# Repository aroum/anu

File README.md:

# Anu

[Anu](https://en.wikipedia.org/wiki/Anu) - compact stick mouse.

Gerber files and stl models can be downloaded in [releases](https://github.com/aroum/anu/releases).

# Features
* PSP analog stick 
* 3 keys, Kailh Choc V1 switches
* Choc spacing
* Direct pins 
* Wireless(optional)
* Per switch RGB(optional)
* Power switch for wireless controllers(optional)
* 100x100 mm panel pcb

# Firmware

Anu can be used with [nRFMicro](https://github.com/joric/nrfmicro) or [nice!nano](https://nicekeyboards.com/nice-nano/) and 301230 batteries for wireless mode. Currently ZMK does not support analog sticks.

The original idea was to create a compact "mouse" ([layout](http://www.keyboard-layout-editor.com/#/gists/458957846f6c65296a02e8bd9ae2c3ca)), but it can also be used as a gamepad. Gamepad firmare use [ArduinoGamepad library](https://github.com/gamelaster/ArduinoGamepad). For more detailed settings of the gamepad, you can use [TocaEdit XBOX 360 CE](https://www.x360ce.com/).

You can use the [threeboard layout](https://github.com/taylorconor/threeboard) to enter text using Anu.

Other configs using the analog stick [1](https://blog.ffff.lt/posts/joystick-algorithms/) & [2](https://github.com/CarrasTec/JoystickQMK/tree/main/macrokrs).

Work on ZMK support is also [in progress](https://github.com/aroum/zmk-anu/).

# BOM

| Item                                                                   | Quantity | Remarks                            |
| ---------------------------------------------------------------------- | -------: | ---------------------------------- |
| [proMicro](https://aliexpress.ru/item/32840365436.html)                |        1 | or any other compatible controller |
| [Kailh Choc V1](https://aliexpress.ru/item/32959996455.html)           |        3  switches                            |
| [FJ08K-S](https://aliexpress.ru/item/1005006435837883.html) or [FJ08K](https://aliexpress.ru/item/32979957864.html)    |       1 | analog stick. FJ08K-S has an additional button  |
| [Keycaps](https://aliexpress.ru/item/33026798318.html)                 |       3 | 1U                                 |
| [YS-SK6812MINI-E](https://aliexpress.ru/item/4000475685852.html)       |       3 | RGB leds                           |
| [Magnets](https://aliexpress.ru/item/1005002757445161.html)            |      3-5 | disc 7x2 mm (for case)             |
| [Bumpon](https://aliexpress.ru/item/4001188580018.html)                |        8 | 5x2 mm                             |
| [Sockets PH3.5](https://aliexpress.ru/item/32899635835.html)           |     12x2 | for controller                     |
| [SMD button 3x4x2mm](https://aliexpress.ru/item/1005003812819985.html) |        1 | for reset                          |
| [MSK-12C02](https://aliexpress.ru/item/1005001398386692.html)          |        1 | Power switch  (wireless only)      |
| [301230](https://aliexpress.ru/item/32732458079.html)                  |        1 | Battery  (wireless only)           |
| [m2 nuts](https://aliexpress.ru/item/1005003114659036.html)            |        4 | for case                           |
| [m2x4 screws](https://aliexpress.ru/item/1005004494509456.html)        |        4 | for case                           |

[IBOM](https://htmlpreview.github.io/?https://github.com/aroum/anu/blob/master/pcb/ibom/ibom.html)

# Build guide
1. Solder the controller sockets
2. Solder the power switch (wireless only)
3. Solder the reset button
4. Solder the battery (only for wireless version)
5. Solder analog stick
6. Solder the pins into the controller
7. Solder 3 Kailh Choc V1 switches 
8. Solder 3 LEDs (RGB version only)
9. Put the keycaps on the switches and analog stick
10. Stick bumpon or place the keyboard in the case
11. Insert controller into sockets
12. Flash the bootloader (see the official manual for the controller)
13. Flash the firmware (see the official manual for the controller)

[Soldering Tutorial for Beginners](https://mightyohm.com/files/soldercomic/FullSolderComic_EN.pdf) ([RU version](https://sho0.neocities.org/downloads/komiks_payat_prosto.pdf))

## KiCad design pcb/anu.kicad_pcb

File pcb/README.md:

# PCB

There is also the option of two PCBs fitted into 100x100 mm.

Gerber files can be downloaded in [releases](https://github.com/aroum/anu/releases).

[IBOM](https://htmlpreview.github.io/?https://github.com/aroum/anu/blob/master/pcb/ibom/ibom.html)

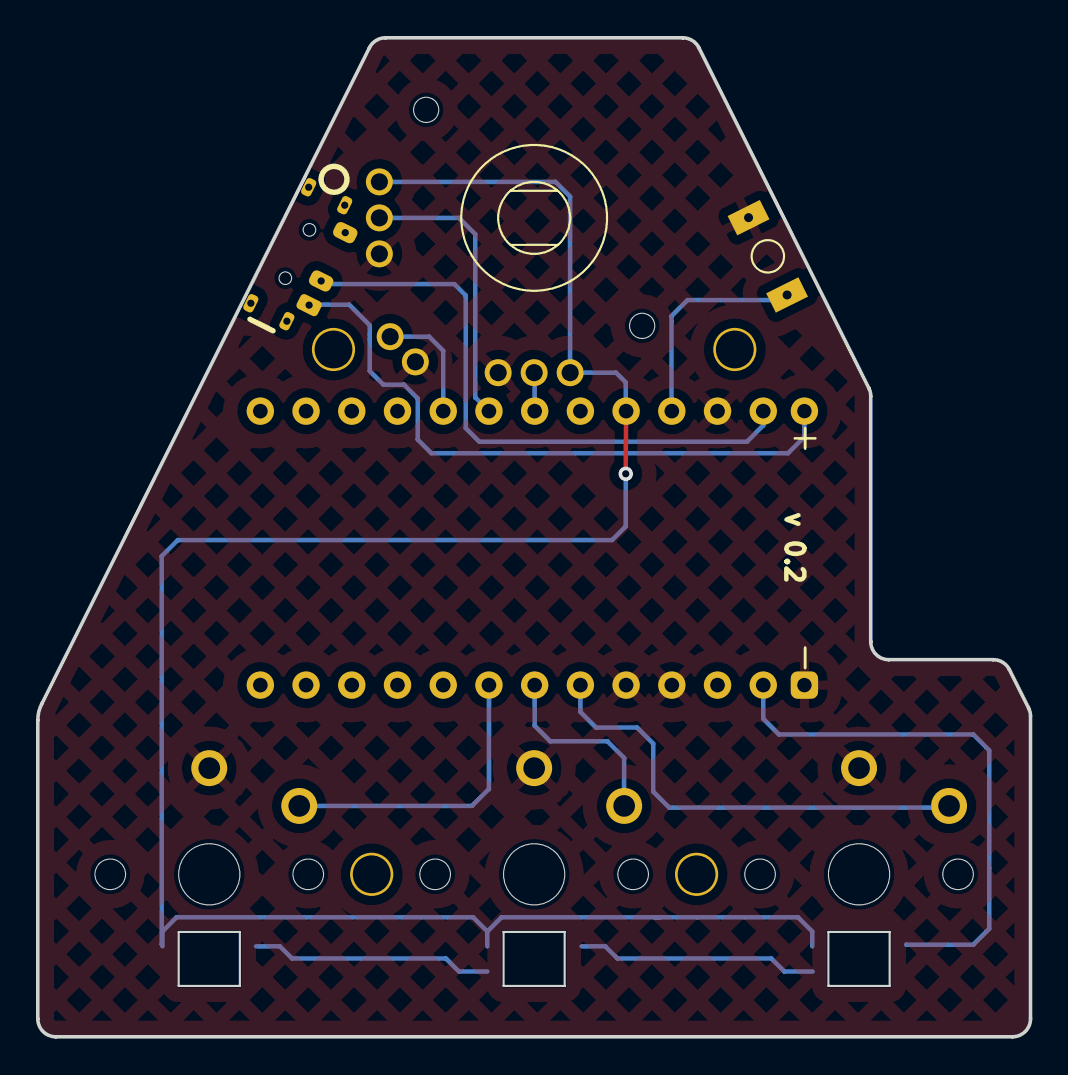
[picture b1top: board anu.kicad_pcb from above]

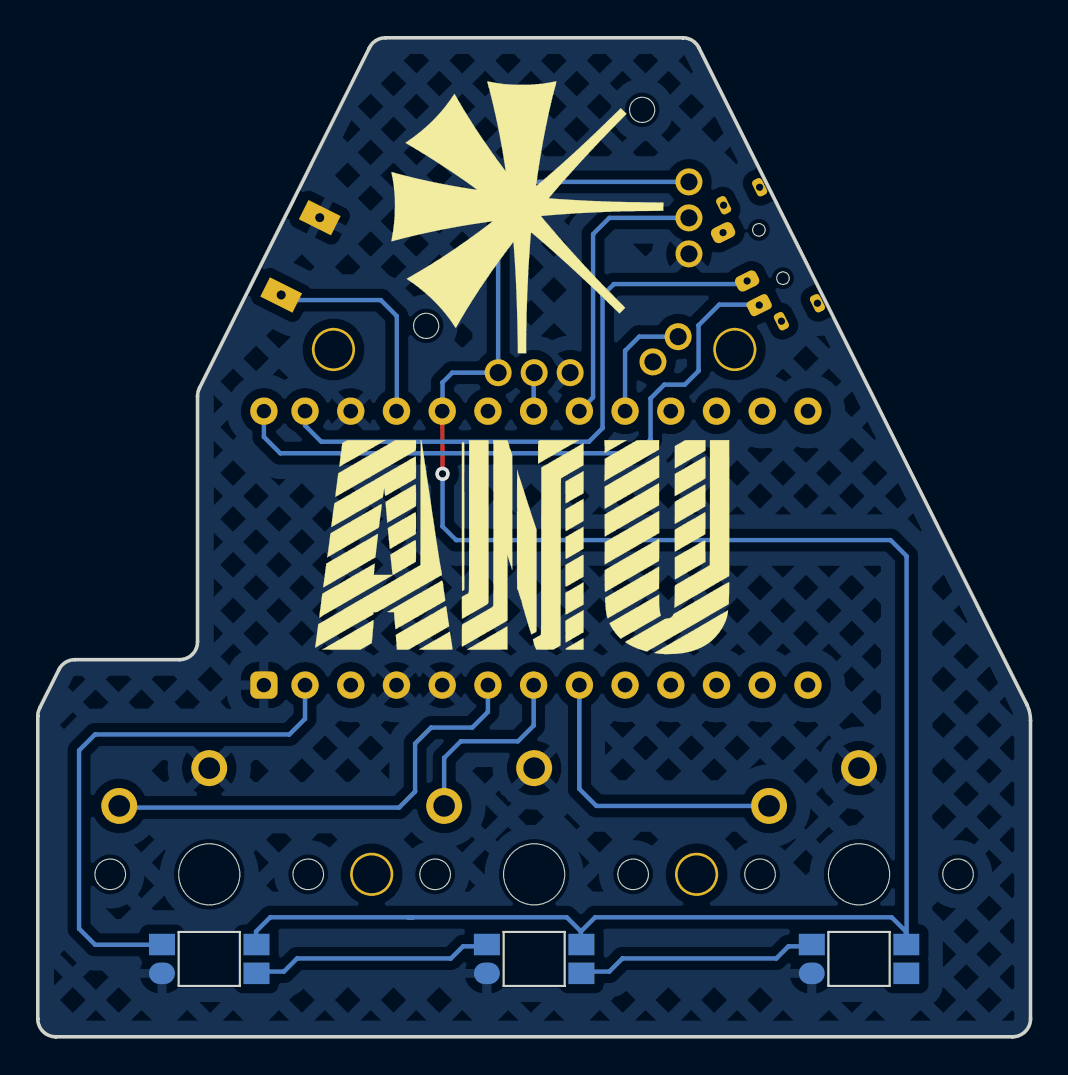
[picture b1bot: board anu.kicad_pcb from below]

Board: 2 copper layers, 55.2 x 55.5 mm, 17 parts (5 on the bottom side), 14 nets.

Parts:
G1: Logo; Logo_anu_cuneiform
G2: Logo; Logo_anu
H1, H1#2, H1#3, H1#4: Hole; HOLE
J1: battery connector; battery_conn_duplex
LED1, LED2, LED3: YS-SK6812MINI-E; YS-SK6812MINI-E_small
RSW1: SW_PUSH; SW_3x4x2_2legs
SW1, SW2, SW3: SW_PUSH; ChocV1_1u
SW4: SW_SPDT; SW_MSK-12C02_duplex
U1: ProMicro_r; ProMicro_v4
X1: FJ08K-S

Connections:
GND: J1.2, LED1.3 (GND), LED2.3 (GND), LED3.3 (GND), RSW1.2, SW1.2, SW2.2, SW3.2, U1.3 (GND), U1.4 (GND), U1.23 (GND), X1.A (SW1), X1.X3 (VCC), X1.Y1 (VCC)
LED: LED3.4 (DIN), U1.1 (D3/TX0)
unnamed: J1.1, SW4.3 (C)
unnamed: LED1.4 (DIN), LED2.2 (DOUT)
unnamed: LED2.4 (DIN), LED3.2 (DOUT)
VBAT: SW4.2 (B), U1.24 (RAW)
VCC: LED1.1 (VDD), LED2.1 (VDD), LED3.1 (VDD), U1.21 (VCC), X1.X1 (GND), X1.Y3 (GND)
analogX: U1.18 (A1/F6), X1.X2 (outX)
analogY: U1.19 (A2/F5), X1.Y2 (outY)
reset: RSW1.1, U1.22 (RST)
sw1: SW1.1, U1.7 (D4/4)
sw2: SW2.1, U1.6 (SCL/D0/3)
sw3: SW3.1, U1.5 (SDA/D1/2)
sw4: U1.17 (A0/F7), X1.B (SW2)

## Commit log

2022-11-29 old qmk
2022-11-29 update QMK config
2024-04-09 add pcb & case
2024-04-09 remove backup folder
2024-04-09 add screws & panels
